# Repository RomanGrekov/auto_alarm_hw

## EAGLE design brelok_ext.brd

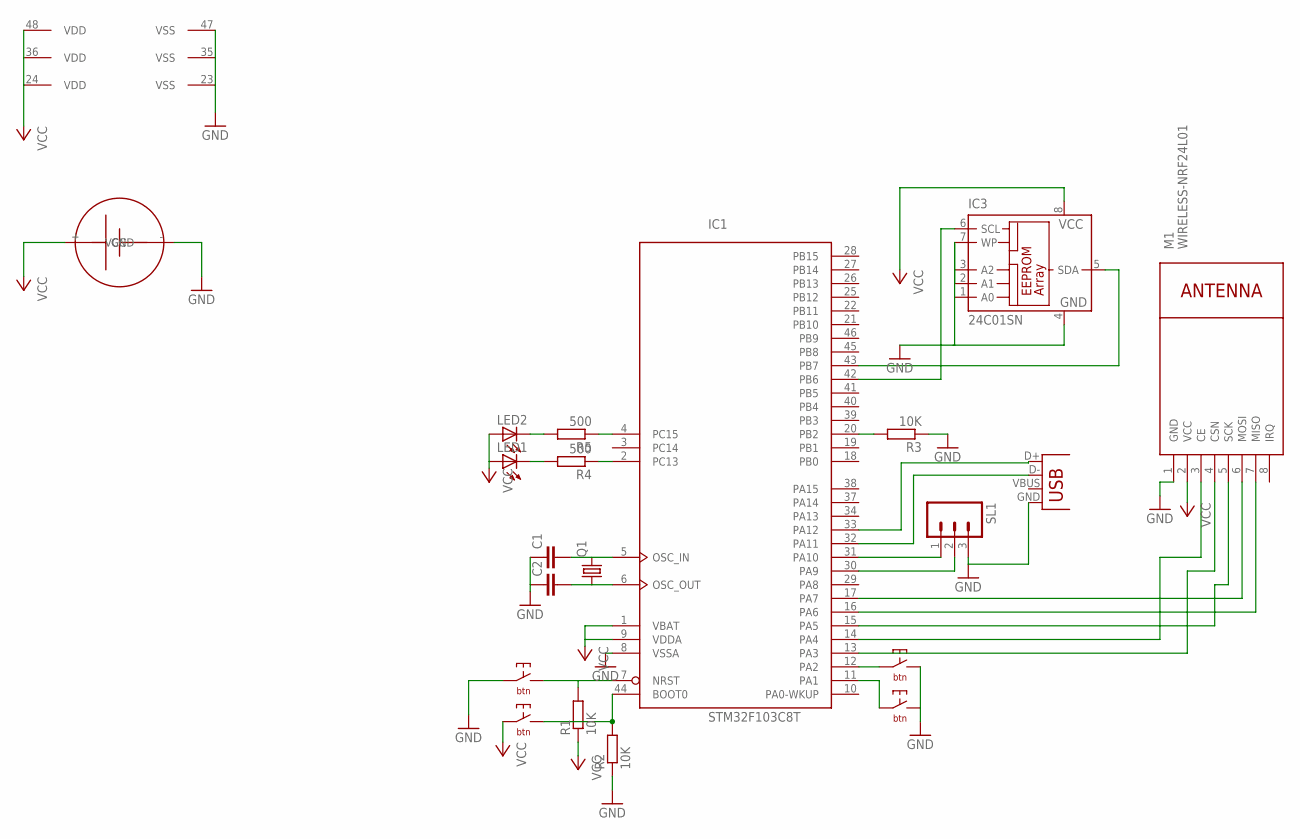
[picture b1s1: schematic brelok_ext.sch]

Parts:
BOOT: TM1103
C1, C2: CC0504; C0504
IC1: STM32F103C8T; LQFP48
IC3: 24C01SN; SO-08
LED1, LED2: LEDCHIP-LED0805; CHIP-LED0805
M1: WIRELESS-NRF24L01
Q1: CRYSTALHC49UP; HC49UP
R1, R2, R3: 10K; R0805
R4, R5: 500; R0805
RESET: TM1103
SL1: M03; 03P
U$2: CR2025_SMD; SMD
USER1, USER2: TM1103
X1: SPARKFUN_USB-MICROB

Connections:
GND: C1.1, C2.1, IC1.8 (VSSA), IC1.23 (VSS), IC1.35 (VSS), IC1.47 (VSS), IC3.1 (A0), IC3.2 (A1), IC3.3 (A2), IC3.4 (GND), IC3.7 (WP), M1.1 (GND), R2.1, R3.1, RESET.P$2, SL1.3, U$2.- (GND), USER1.P$1, USER2.P$1, X1.GND
unnamed: IC1.17 (PA7), M1.6 (MOSI)
unnamed: IC1.16 (PA6), M1.7 (MISO)
unnamed: IC1.15 (PA5), M1.5 (SCK)
unnamed: IC1.14 (PA4), M1.3 (CE)
unnamed: IC1.13 (PA3), M1.4 (CSN)
unnamed: C1.2, IC1.5 (OSC_IN), Q1.2
unnamed: C2.2, IC1.6 (OSC_OUT), Q1.1
unnamed: IC1.7 (NRST), R1.2, RESET.P$1
unnamed: BOOT.P$1, IC1.44 (BOOT0), R2.2
unnamed: IC1.31 (PA10), SL1.1
unnamed: IC1.20 (PB2), R3.2
unnamed: IC1.30 (PA9), SL1.2
unnamed: LED1.C, R4.2
unnamed: LED2.C, R5.2
unnamed: IC1.4 (PC15), R5.1
unnamed: IC1.2 (PC13), R4.1
unnamed: IC1.12 (PA2), USER2.P$2
unnamed: IC1.11 (PA1), USER1.P$2
unnamed: IC1.42 (PB6), IC3.6 (SCL)
unnamed: IC1.43 (PB7), IC3.5 (SDA)
unnamed: IC1.32 (PA11), X1.D-
unnamed: IC1.33 (PA12), X1.D+
VCC: BOOT.P$2, IC1.1 (VBAT), IC1.9 (VDDA), IC1.24 (VDD), IC1.36 (VDD), IC1.48 (VDD), IC3.8 (VCC), LED1.A, LED2.A, M1.2 (VCC), R1.1, U$2.+ (VCC)

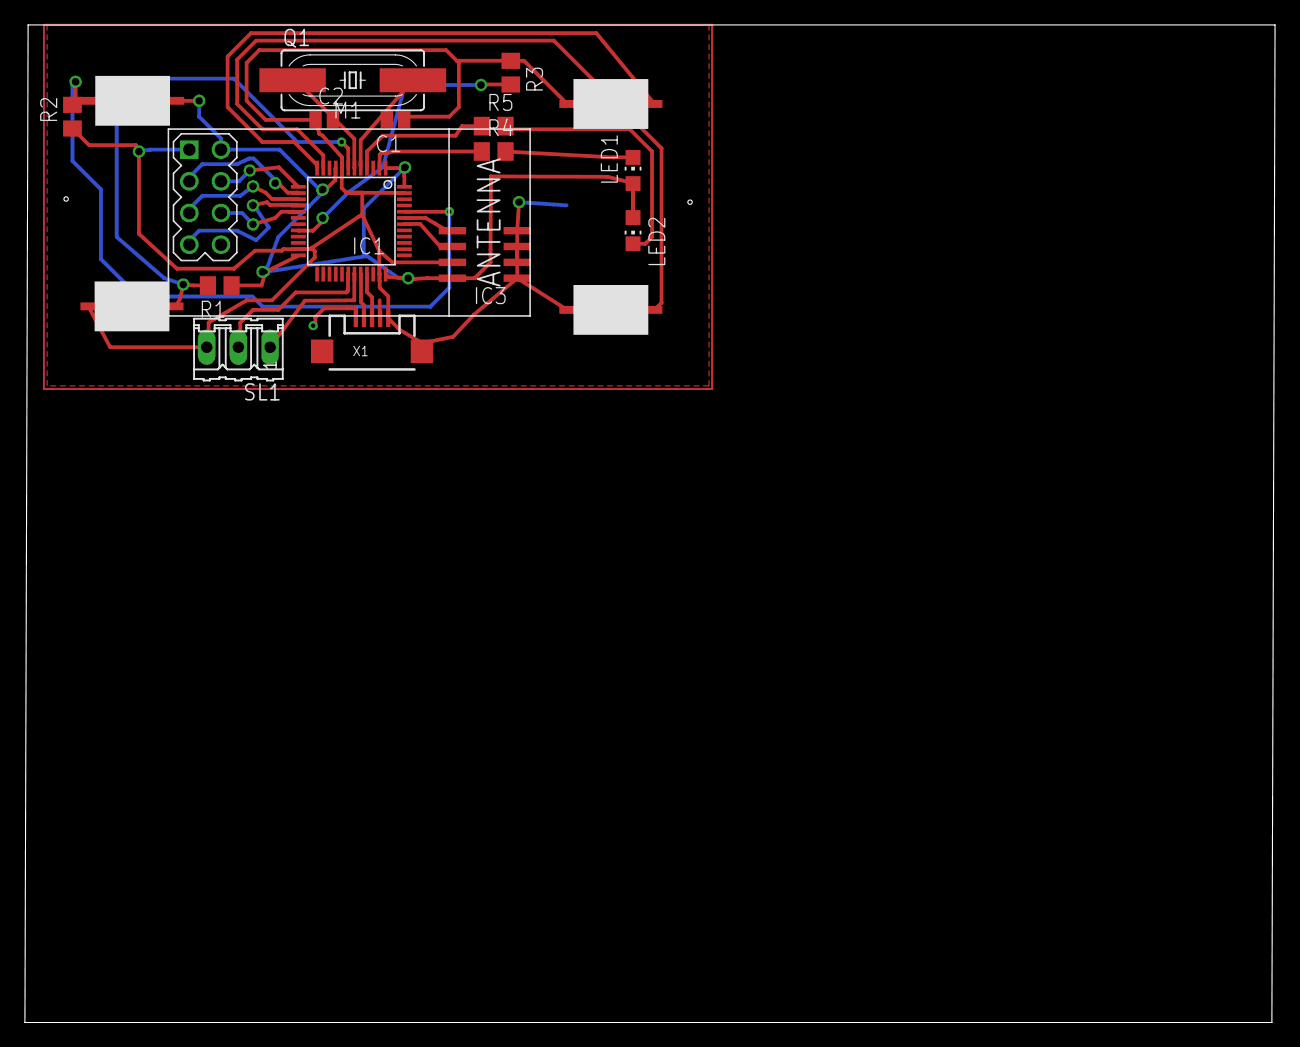
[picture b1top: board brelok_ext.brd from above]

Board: 2 copper layers, 100.3 x 80.0 mm, 20 parts (1 on the bottom side), 24 nets.

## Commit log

2017-11-22 Made working prototype

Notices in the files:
parts and their libraries:
diy-modules: Released under the Creative Commons Attribution 4.0 International License: http://creativecommons.org/licenses/by/4.0
